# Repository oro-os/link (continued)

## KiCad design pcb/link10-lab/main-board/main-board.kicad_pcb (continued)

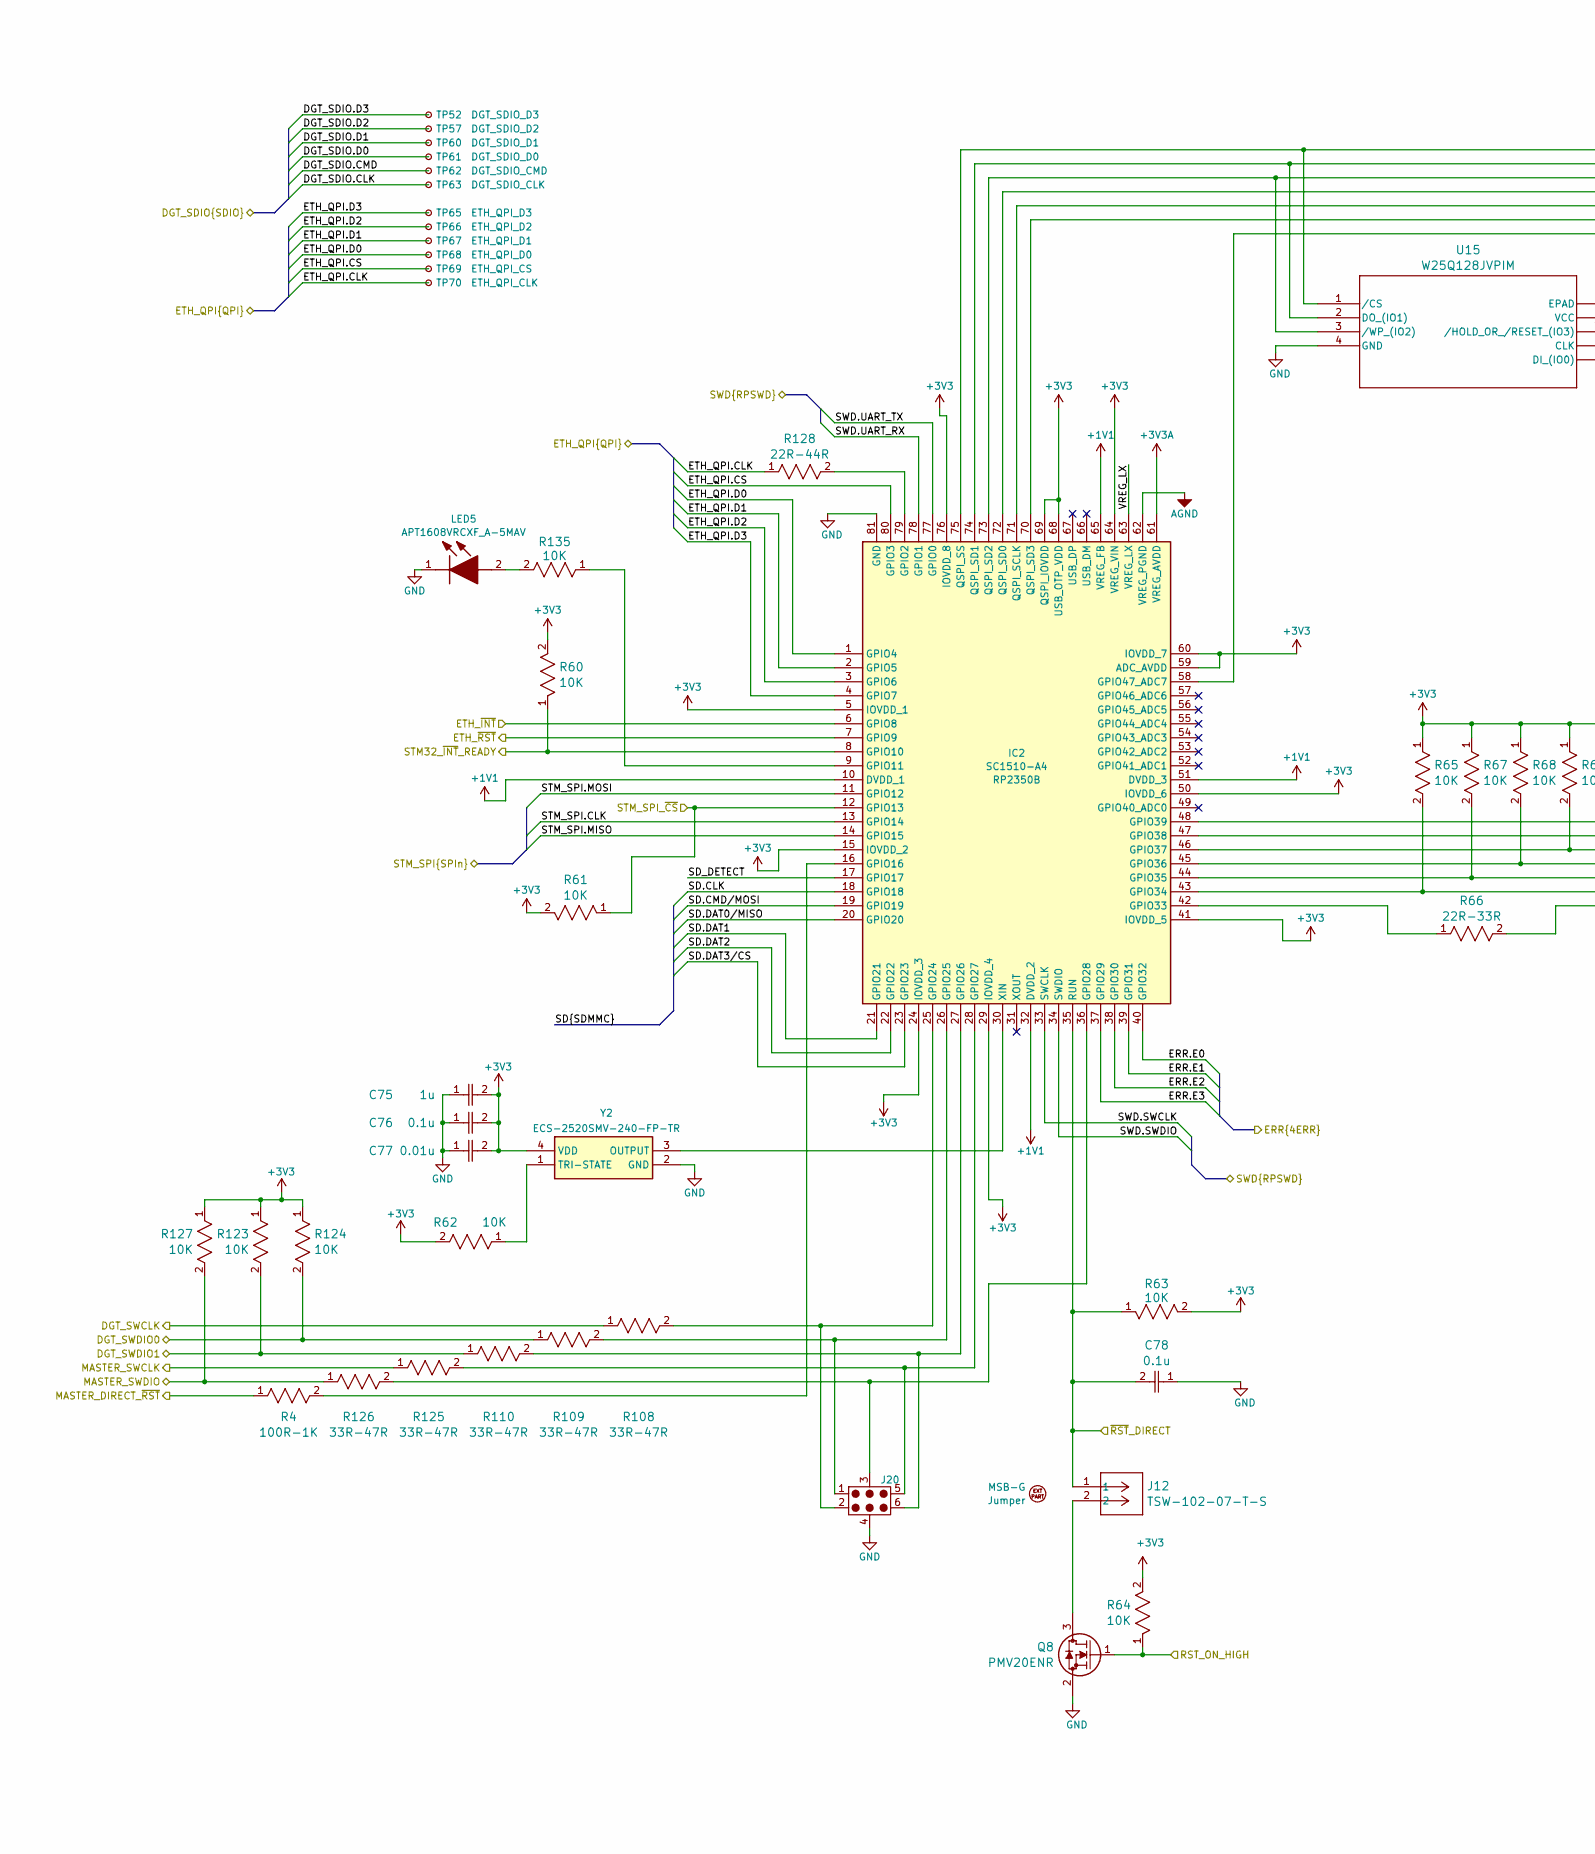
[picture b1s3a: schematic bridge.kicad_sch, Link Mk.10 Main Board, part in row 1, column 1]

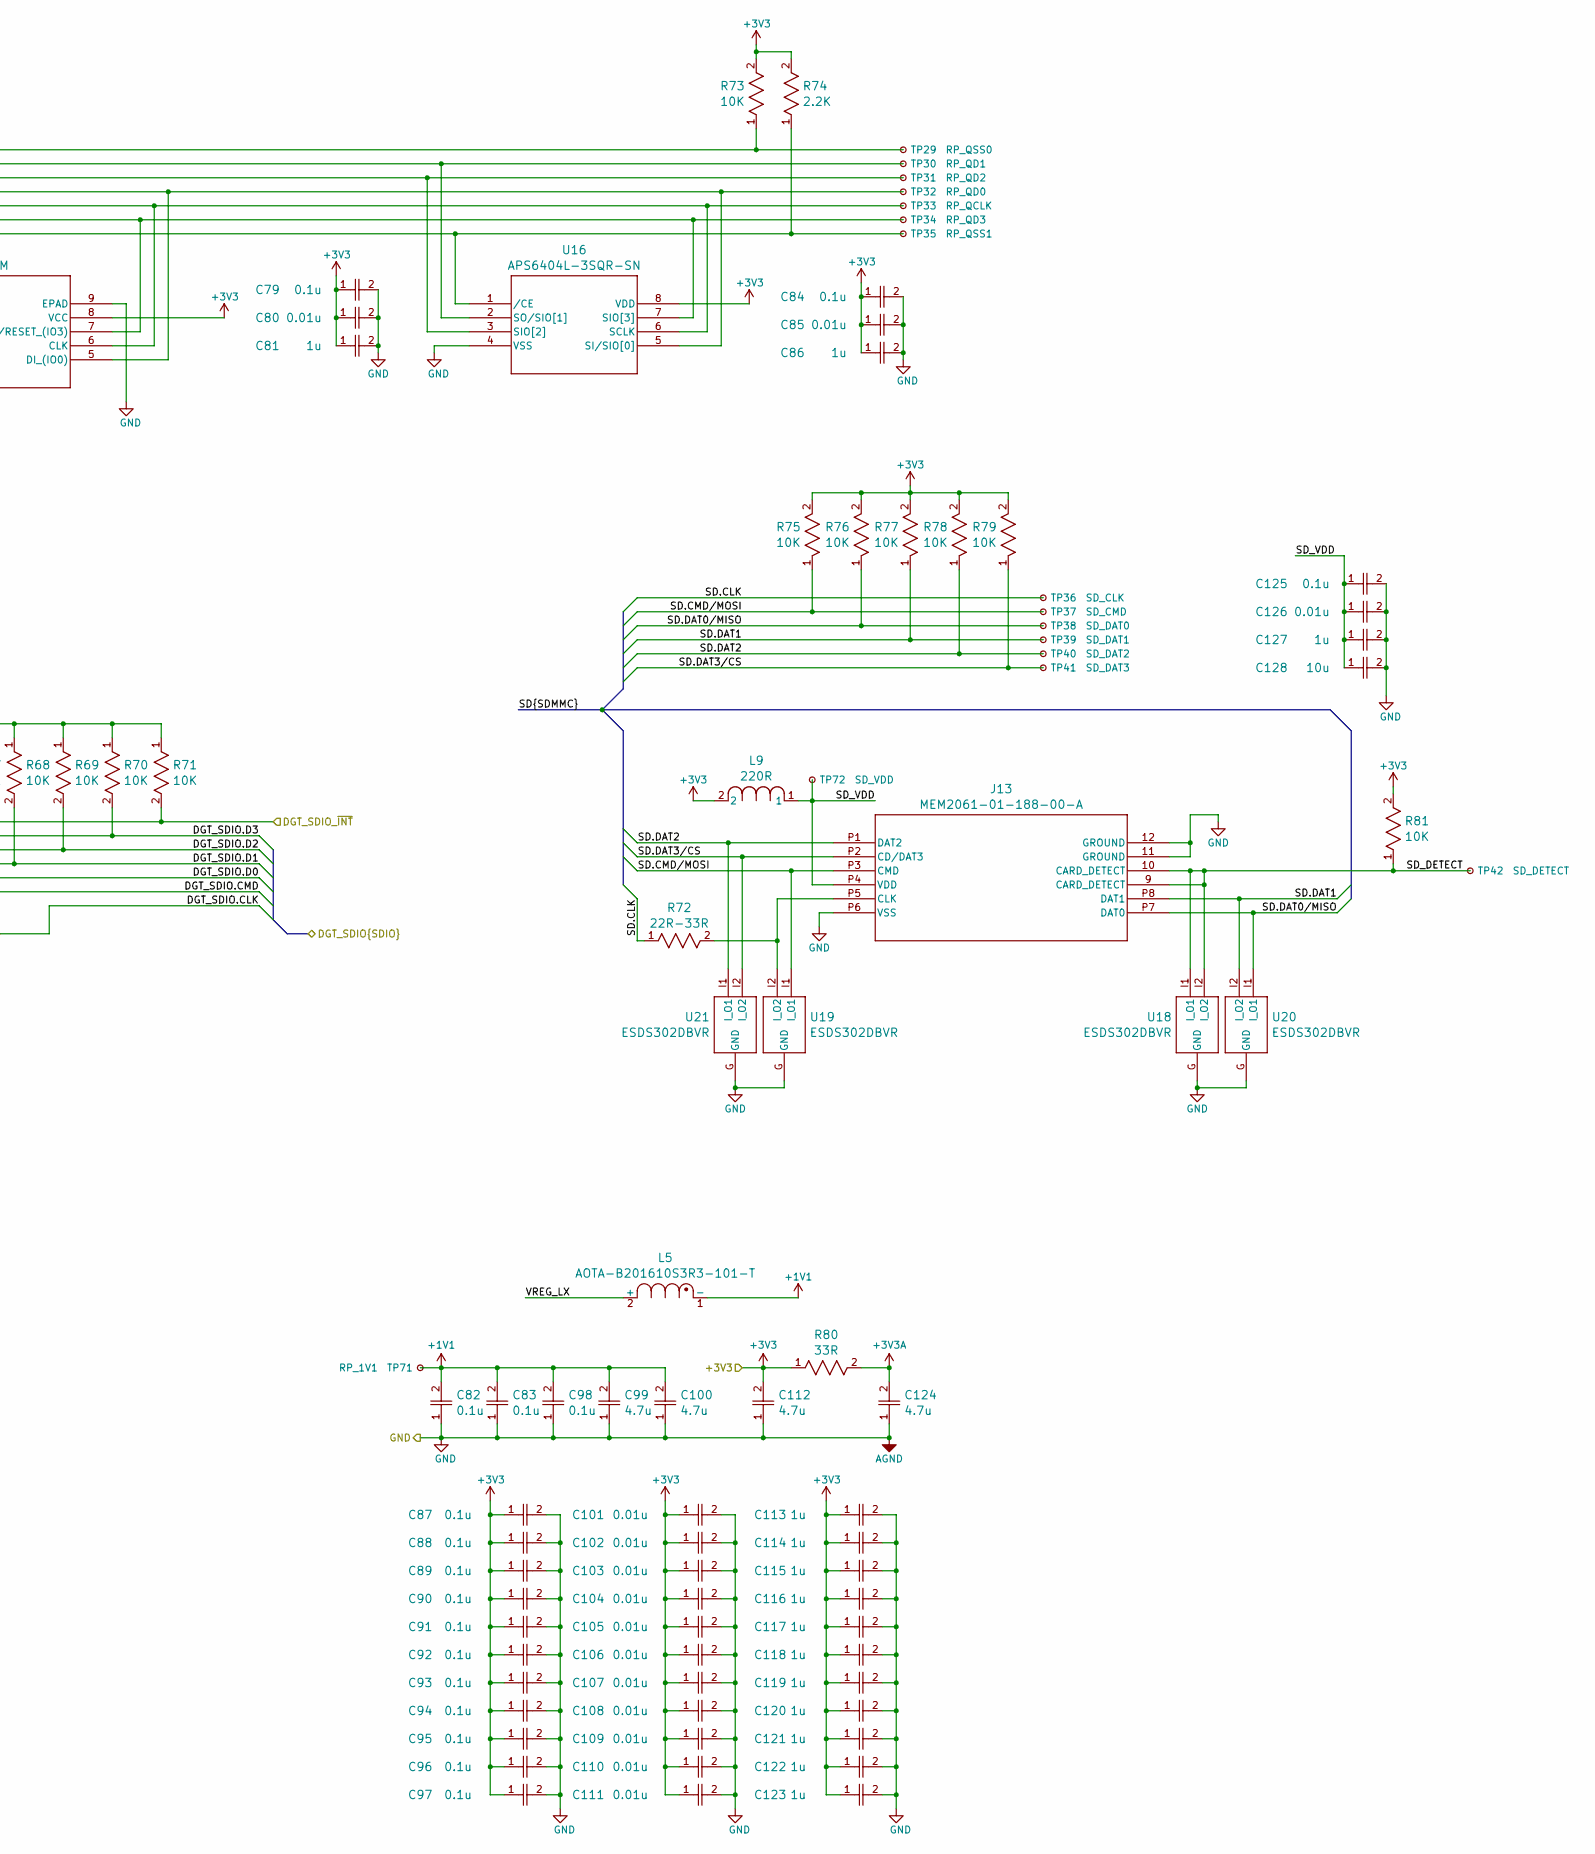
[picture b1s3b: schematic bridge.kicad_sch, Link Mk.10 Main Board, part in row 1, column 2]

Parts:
C75, C81, C86, C113, C114, C115, C116, C117, C118, C119, C120, C121, C122, C123, C127: 1u; OP_0001R; DigiKey ID 587-3766-1-ND
C76, C78, C79, C82, C83, C84, C87, C88, C89, C90, C91, C92, C93, C94, C95, C96, C97, C98, C125: 0.1u; OP_0001Y; DigiKey ID 587-MSAST1L3YB5104KFNA01CT-ND
C77, C80, C85, C101, C102, C103, C104, C105, C106, C107, C108, C109, C110, C111, C126: 0.01u; OP_0000F; Mouser ID 791-0402B103J160CT
C99, C100, C112, C124: 4.7u; OP_00014; Manufacturer_Part_Number GRM155C61E475ME15J; DigiKey ID 1276-1480-6-ND
C128: 10u; OP_0001M; Mouser P/N 81-GRM188R61E106MA3D; Mouser ID 81-GRM188R61E106MA3D
EXT4: MSB-G; Mouser P/N 737-MSB-G; Digi-Key P/N 2057-MSB-G-ND
IC2: SC1510-A4; OP_00050; Manufacturer_Part_Number SC1510-A4; Digi-Key P/N 2648-SC1510-A4CT-ND, 2648-SC1510-A4DKR-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
J12: TSW-102-07-T-S; OP_00079; Mouser P/N 200-TSW10207TS; Digi-Key P/N 612-TSW-102-07-T-S-ND
J13: MEM2061-01-188-00-A; OP_0001X; Mouser ID 640-MEM20610118800A
J20: CPG-81-TH-B-Pads; CPG-81-TH-B-Landing
L5: AOTA-B201610S3R3-101-T; OP_00073; Mouser P/N 815-AB201610S3R3101T; Digi-Key P/N 535-AOTA-B201610S3R3-101-TCT-ND, 535-AO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
L9: 220R; OP_0000Y; Mouser P/N 81-BLM18PG221SN1D; DigiKey ID 490-5221-1-ND
LED5: APT1608VRCXF_A-5MAV; OP_0000U; Manufacturer_Part_Number APT1608VRCXF/A-5MAV; Mouser Part Number 604-APT1608VRCXF5MAV
Q8: PMV20ENR; OP_0001Z; DigiKey ID 1727-2301-1-ND
R4: 100R-1K; OP_0003D; Mouser P/N 660-SG73P2ATTD102J; Digi-Key P/N 2019-SG73P2ATTD102JCT-ND, 2019-SG73P2AT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
R60, R61, R62, R63, R64, R65, R67, R68, R69, R70, R71, R73, R75, R76, R77, R78, R79, R81, R123, R124, R127, R135: 10K; OP_00021; DigiKey ID RMCF0402FT10K0CT-ND
R66, R72: 22R-33R; OP_00022; Mouser P/N 754-RR0510R-330D; DigiKey ID RR05R33DCT-ND
R74: 2.2K; OP_0002S; Mouser P/N 667-ERJ-P06F2321V; Digi-Key P/N ERJ-P06F2321V-ND
R80: 33R; OP_00022; Mouser P/N 754-RR0510R-330D; DigiKey ID RR05R33DCT-ND
R108, R109, R110, R125, R126: 33R-47R; OP_0005Y; Mouser P/N 652-CR0603FX-43R2ELF; Digi-Key P/N CR0603-FX-43R2ELFCT-ND, CR0603-FX-43R2E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
R128: 22R-44R; OP_0005Y; Mouser P/N 652-CR0603FX-43R2ELF; Digi-Key P/N CR0603-FX-43R2ELFCT-ND, CR0603-FX-43R2E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
TP29: RP_QSS0; TestPoint_Pad_D1.0mm
TP30: RP_QD1; TestPoint_Pad_D1.0mm
TP31: RP_QD2; TestPoint_Pad_D1.0mm
TP32: RP_QD0; TestPoint_Pad_D1.0mm
TP33: RP_QCLK; TestPoint_Pad_D1.0mm
TP34: RP_QD3; TestPoint_Pad_D1.0mm
TP35: RP_QSS1; TestPoint_Pad_D1.0mm
TP36: SD_CLK; TestPoint_Pad_D1.0mm
TP37: SD_CMD; TestPoint_Pad_D1.0mm
TP38: SD_DAT0; TestPoint_Pad_D1.0mm
TP39: SD_DAT1; TestPoint_Pad_D1.0mm
TP40: SD_DAT2; TestPoint_Pad_D1.0mm
TP41: SD_DAT3; TestPoint_Pad_D1.0mm
TP42: SD_DETECT; TestPoint_Pad_D1.0mm
TP52: DGT_SDIO_D3; TestPoint_Pad_D1.0mm
TP57: DGT_SDIO_D2; TestPoint_Pad_D1.0mm
TP60: DGT_SDIO_D1; TestPoint_Pad_D1.0mm
TP61: DGT_SDIO_D0; TestPoint_Pad_D1.0mm
TP62: DGT_SDIO_CMD; TestPoint_Pad_D1.0mm
TP63: DGT_SDIO_CLK; TestPoint_Pad_D1.0mm
TP65: ETH_QPI_D3; TestPoint_Pad_D1.0mm
TP66: ETH_QPI_D2; TestPoint_Pad_D1.0mm
TP67: ETH_QPI_D1; TestPoint_Pad_D1.0mm
TP68: ETH_QPI_D0; TestPoint_Pad_D1.0mm
TP69: ETH_QPI_CS; TestPoint_Pad_D1.0mm
TP70: ETH_QPI_CLK; TestPoint_Pad_D1.0mm
TP71: RP_1V1; TestPoint_Pad_2.0x2.0mm
TP72: SD_VDD; TestPoint_Pad_2.0x2.0mm
U15: W25Q128JVPIM; OP_00054; Mouser P/N 454-W25Q128JVPIMTR; Digi-Key P/N 256-W25Q128JVPIM-TUBE-ND, 256-W25Q128JV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
U16: APS6404L-3SQR-SN; OP_00055; Mouser P/N 878-APS6404L-3SQR-SN
U18, U19, U20, U21: ESDS302DBVR; OP_0003B; Mouser P/N 595-ESDS302DBVR; Digi-Key P/N 296-51110-1-ND, 296-51110-2-ND, 296-511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
Y2: ECS-2520SMV-240-FP-TR; OP_0001E; Manufacturer_Part_Number ECS-2520SMV-240-FP-TR; Mouser Part Number 520-2520SMV-240-FP-T

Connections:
+3V3_STM: C75.2, C76.2, C77.2, C79.1, C80.1, C81.1, C84.1, C85.1, C86.1, C87.1, C88.1, C89.1, C90.1, C91.1, C92.1, C93.1, C94.1, C95.1, C96.1, C97.1, C101.1, C102.1, C103.1, C104.1, C105.1, C106.1, C107.1, C108.1, C109.1, C110.1, C111.1, C112.2, C113.1, C114.1, C115.1, C116.1, C117.1, C118.1, C119.1, C120.1, C121.1, C122.1, C123.1, IC2.5 (IOVDD_1), IC2.15 (IOVDD_2), IC2.24 (IOVDD_3), IC2.29 (IOVDD_4), IC2.41 (IOVDD_5), IC2.50 (IOVDD_6), IC2.59 (ADC_AVDD), IC2.60 (IOVDD_7), IC2.64 (VREG_VIN), IC2.68 (USB_OTP_VDD), IC2.69 (QSPI_IOVDD), IC2.76 (IOVDD_8), L9.2, R60.2, R61.2, R62.2, R63.2, R64.2, R65.1, R67.1, R68.1, R69.1, R70.1, R71.1, R73.2, R74.2, R75.2, R76.2, R77.2, R78.2, R79.2, R80.1, R81.2, R123.1, R124.1, R127.1, U15.8 (VCC), U16.8 (VDD), Y2.4 (VDD); also elsewhere on the board
/BRIDGE_DIRECT_RST: C78.2, IC2.35 (RUN), J12.1, R63.1; also elsewhere on the board
/BRIDGE_INT: IC2.8 (GPIO10), R60.1; also elsewhere on the board
/BRIDGE_SWD.SWCLK: IC2.33 (SWCLK); also elsewhere on the board
/BRIDGE_SWD.SWDIO: IC2.34 (SWDIO); also elsewhere on the board
/BRIDGE_SWD.UART_RX: IC2.78 (GPIO1); also elsewhere on the board
/BRIDGE_SWD.UART_TX: IC2.77 (GPIO0); also elsewhere on the board
/Baseboard/RP_ERR.E0: IC2.40 (GPIO32); also elsewhere on the board
/Baseboard/RP_ERR.E1: IC2.39 (GPIO31); also elsewhere on the board
/Baseboard/RP_ERR.E2: IC2.38 (GPIO30); also elsewhere on the board
/Baseboard/RP_ERR.E3: IC2.37 (GPIO29); also elsewhere on the board
/Baseboard/SPI1.CLK: IC2.13 (GPIO14); also elsewhere on the board
/Baseboard/SPI1.MISO: IC2.14 (GPIO15); also elsewhere on the board
/Baseboard/SPI1.MOSI: IC2.11 (GPIO12); also elsewhere on the board
/Bridge (RP) + SD/+1V1: C82.2, C83.2, C98.2, C99.2, C100.2, IC2.10 (DVDD_1), IC2.32 (DVDD_2), IC2.51 (DVDD_3), IC2.65 (VREG_FB), L5.1 (-), TP71.1 (1_1)
/Bridge (RP) + SD/+3V3A: C124.2, IC2.61 (VREG_AVDD), R80.2
/Bridge (RP) + SD/DGT_SDIO.CLK: R66.2, TP63.1 (1_1); also elsewhere on the board
/Bridge (RP) + SD/DGT_SDIO.CMD: IC2.43 (GPIO34), R65.2, TP62.1 (1_1); also elsewhere on the board
/Bridge (RP) + SD/DGT_SDIO.D0: IC2.44 (GPIO35), R67.2, TP61.1 (1_1); also elsewhere on the board
/Bridge (RP) + SD/DGT_SDIO.D1: IC2.45 (GPIO36), R68.2, TP60.1 (1_1); also elsewhere on the board
/Bridge (RP) + SD/DGT_SDIO.D2: IC2.46 (GPIO37), R69.2, TP57.1 (1_1); also elsewhere on the board
/Bridge (RP) + SD/DGT_SDIO.D3: IC2.47 (GPIO38), R70.2, TP52.1 (1_1); also elsewhere on the board
/Bridge (RP) + SD/DGT_SWCLK: R108.1; also elsewhere on the board
/Bridge (RP) + SD/DGT_SWDIO0: R109.1, R124.2; also elsewhere on the board
/Bridge (RP) + SD/DGT_SWDIO1: R110.1, R123.2; also elsewhere on the board
/Bridge (RP) + SD/ETH_QPI.CLK: R128.1, TP70.1 (1_1); also elsewhere on the board
/Bridge (RP) + SD/ETH_QPI.CS: IC2.80 (GPIO3), TP69.1 (1_1); also elsewhere on the board
/Bridge (RP) + SD/ETH_QPI.D0: IC2.1 (GPIO4), TP68.1 (1_1); also elsewhere on the board
/Bridge (RP) + SD/ETH_QPI.D1: IC2.2 (GPIO5), TP67.1 (1_1); also elsewhere on the board
/Bridge (RP) + SD/ETH_QPI.D2: IC2.3 (GPIO6), TP66.1 (1_1); also elsewhere on the board
/Bridge (RP) + SD/ETH_QPI.D3: IC2.4 (GPIO7), TP65.1 (1_1); also elsewhere on the board
/Bridge (RP) + SD/ETH_~INT: IC2.6 (GPIO8); also elsewhere on the board
/Bridge (RP) + SD/ETH_~RST: IC2.7 (GPIO9); also elsewhere on the board
/Bridge (RP) + SD/SD.CLK: IC2.18 (GPIO18), R72.1, TP36.1 (1_1)
/Bridge (RP) + SD/SD.CMD/MOSI: IC2.19 (GPIO19), J13.P3 (CMD), R75.1, TP37.1 (1_1), U19.I1 (I_O1)
/Bridge (RP) + SD/SD.DAT0/MISO: IC2.20 (GPIO20), J13.P7 (DAT0), R76.1, TP38.1 (1_1), U20.I1 (I_O1)
/Bridge (RP) + SD/SD.DAT1: IC2.21 (GPIO21), J13.P8 (DAT1), R77.1, TP39.1 (1_1), U20.I2 (I_O2)
/Bridge (RP) + SD/SD.DAT2: IC2.22 (GPIO22), J13.P1 (DAT2), R78.1, TP40.1 (1_1), U21.I1 (I_O1)
/Bridge (RP) + SD/SD.DAT3/CS: IC2.23 (GPIO23), J13.P2 (CD/DAT3), R79.1, TP41.1 (1_1), U21.I2 (I_O2)
/Bridge (RP) + SD/SD_DETECT: IC2.17 (GPIO17), J13.9 (CARD_DETECT), J13.10 (CARD_DETECT), R81.1, TP42.1 (1_1), U18.I1 (I_O1), U18.I2 (I_O2)
/Bridge (RP) + SD/SD_VDD: C125.1, C126.1, C127.1, C128.1, J13.P4 (VDD), L9.1, TP72.1 (1_1)
/Bridge (RP) + SD/STM_SPI_~CS: IC2.12 (GPIO13), R61.1; also elsewhere on the board
/Bridge (RP) + SD/VREG_LX: IC2.63 (VREG_LX), L5.2 (+)
/DGT_SDIO_INT: IC2.48 (GPIO39), R71.2; also elsewhere on the board
/MASTER_DIRECT_RST: R4.1; also elsewhere on the board
/MASTER_SWD.SWCLK: R125.1; also elsewhere on the board
/MASTER_SWD.SWDIO: R126.1, R127.2; also elsewhere on the board
/RP_BB_RST: Q8.1 (G), R64.1; also elsewhere on the board
GND: C75.1, C76.1, C77.1, C78.1, C79.2, C80.2, C81.2, C82.1, C83.1, C84.2, C85.2, C86.2, C87.2, C88.2, C89.2, C90.2, C91.2, C92.2, C93.2, C94.2, C95.2, C96.2, C97.2, C98.1, C99.1, C100.1, C101.2, C102.2, C103.2, C104.2, C105.2, C106.2, C107.2, C108.2, C109.2, C110.2, C111.2, C112.1, C113.2, C114.2, C115.2, C116.2, C117.2, C118.2, C119.2, C120.2, C121.2, C122.2, C123.2, C124.1, C125.2, C126.2, C127.2, C128.2, IC2.62 (VREG_PGND), IC2.81 (GND), J13.11 (GROUND), J13.12 (GROUND), J13.P6 (VSS), J20.4, LED5.1 (K), Q8.2 (S), U15.4 (GND), U15.9 (EPAD), U16.4 (VSS), U18.G (GND), U19.G (GND), U20.G (GND), U21.G (GND), Y2.2 (GND); also elsewhere on the board
unnamed: IC2.79 (GPIO2), R128.2
unnamed: IC2.9 (GPIO11), R135.1
unnamed: IC2.16 (GPIO16), R4.2
unnamed: IC2.25 (GPIO24), J20.2, R108.2
unnamed: IC2.26 (GPIO25), J20.1, R109.2
unnamed: IC2.27 (GPIO26), J20.6, R110.2
unnamed: IC2.28 (GPIO27), J20.5, R125.2
unnamed: IC2.36 (GPIO28), J20.3, R126.2
unnamed: IC2.42 (GPIO33), R66.1
unnamed: IC2.58 (GPIO47_ADC7), R74.1, TP35.1 (1_1), U16.1 (/CE)
unnamed: IC2.71 (QSPI_SCLK), TP33.1 (1_1), U15.6 (CLK), U16.6 (SCLK)
unnamed: IC2.72 (QSPI_SD0), TP32.1 (1_1), U15.5 (DI_(IO0)), U16.5 (SI/SIO[0])
unnamed: IC2.74 (QSPI_SD1), TP30.1 (1_1), U15.2 (DO_(IO1)), U16.2 (SO/SIO[1])
unnamed: IC2.73 (QSPI_SD2), TP31.1 (1_1), U15.3 (/WP_(IO2)), U16.3 (SIO[2])
unnamed: IC2.70 (QSPI_SD3), TP34.1 (1_1), U15.7 (/HOLD_OR_/RESET_(IO3)), U16.7 (SIO[3])
unnamed: IC2.75 (QSPI_SS), R73.1, TP29.1 (1_1), U15.1 (/CS)
unnamed: IC2.30 (XIN), Y2.3 (OUTPUT)
unnamed: J13.P5 (CLK), R72.2, U19.I2 (I_O2)
unnamed: LED5.2 (A), R135.2
unnamed: J12.2, Q8.3 (D)
unnamed: R62.1, Y2.1 (TRI-STATE)

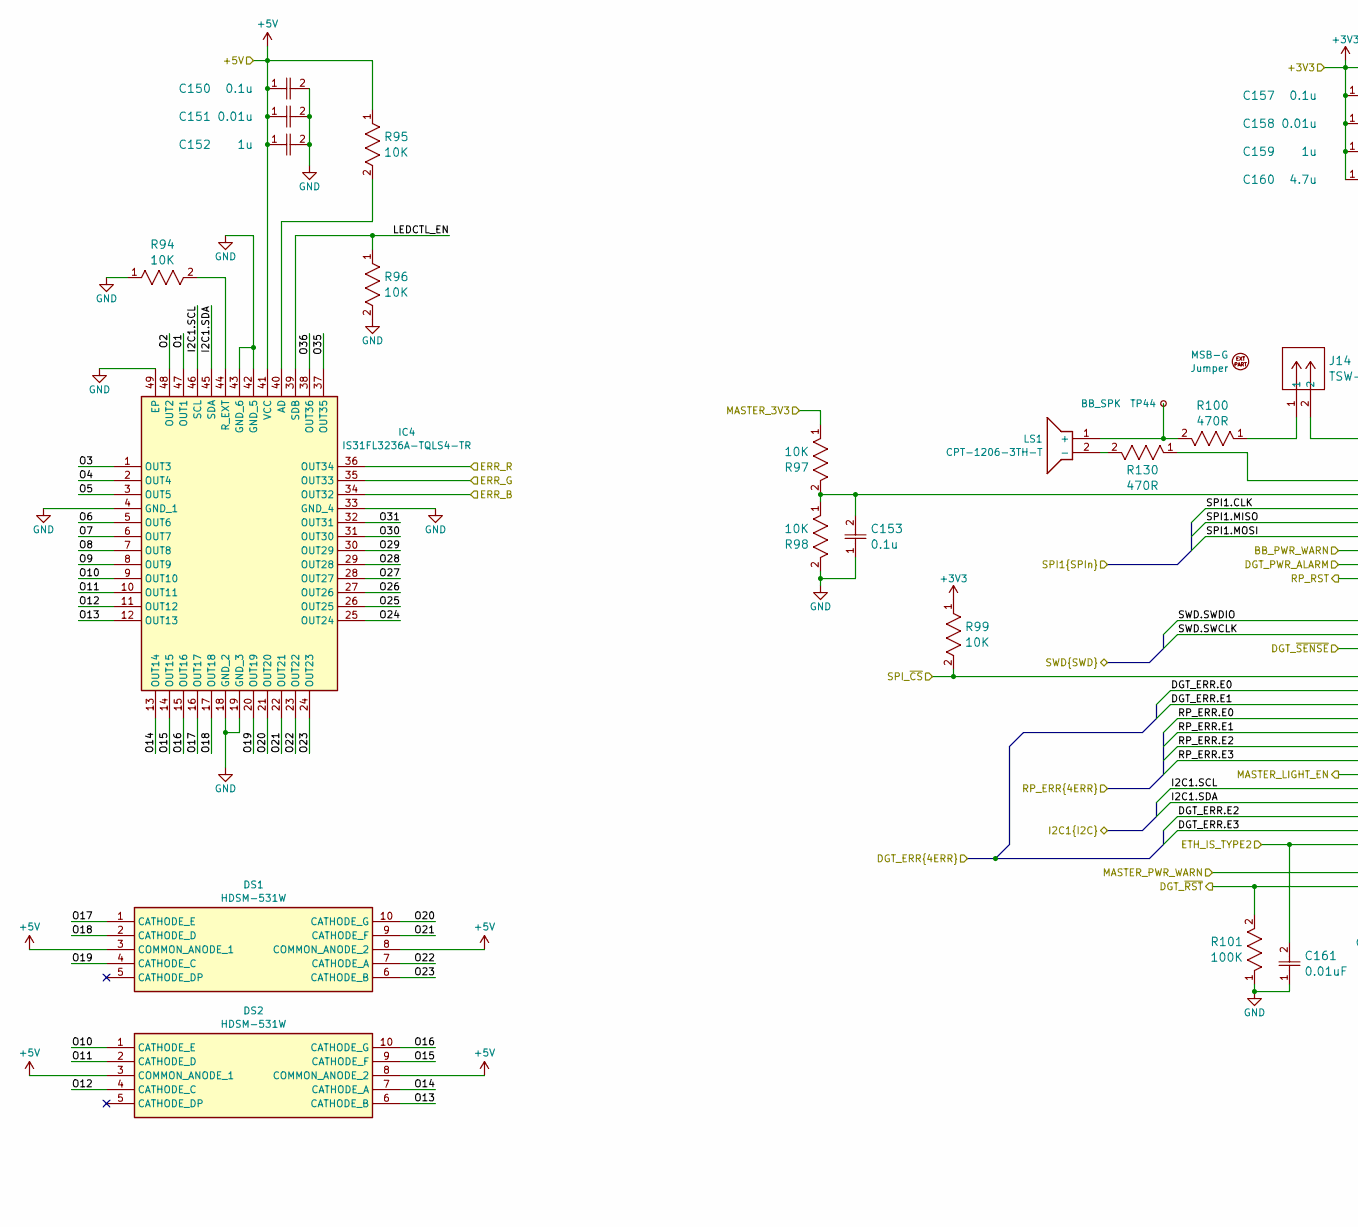
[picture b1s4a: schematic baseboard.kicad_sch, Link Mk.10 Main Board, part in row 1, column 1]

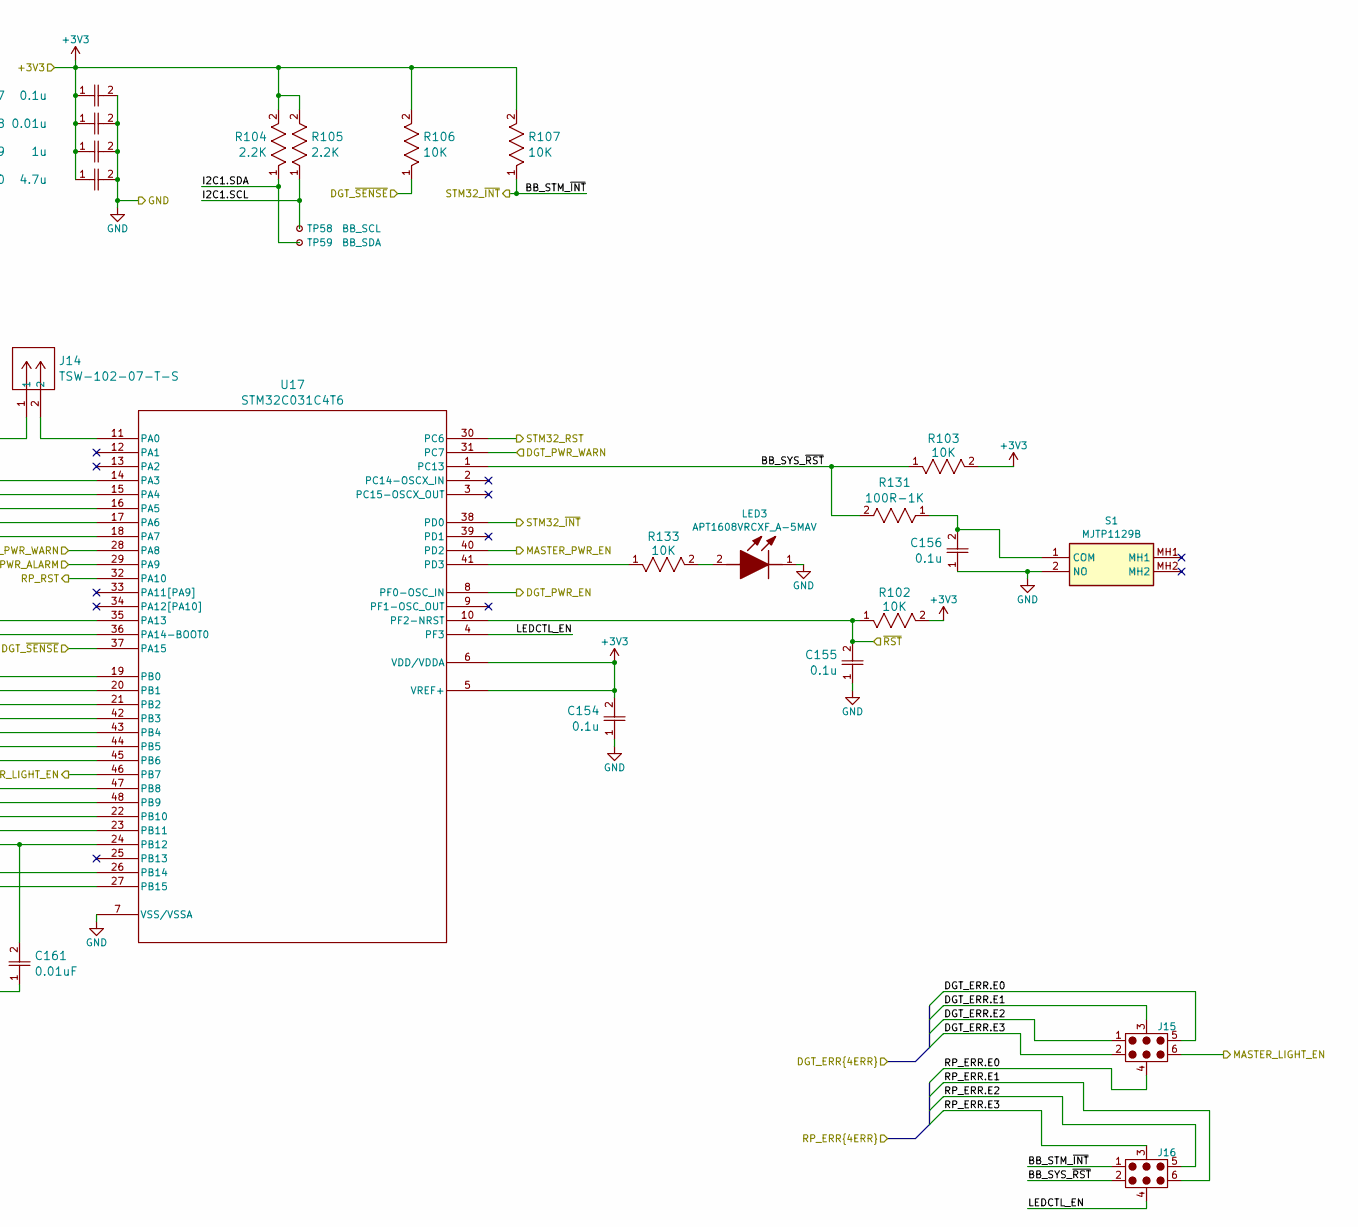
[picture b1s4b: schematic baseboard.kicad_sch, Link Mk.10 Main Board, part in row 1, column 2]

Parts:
C150, C153, C154, C155, C156, C157: 0.1u; OP_0001Y; DigiKey ID 587-MSAST1L3YB5104KFNA01CT-ND
C151, C158: 0.01u; OP_0000F; Mouser ID 791-0402B103J160CT
C152, C159: 1u; OP_0001R; DigiKey ID 587-3766-1-ND
C160: 4.7u; OP_00014; Manufacturer_Part_Number GRM155C61E475ME15J; DigiKey ID 1276-1480-6-ND
C161: 0.01uF; OP_0000F; Mouser ID 791-0402B103J160CT
DS1, DS2: HDSM-531W; OP_00077; Manufacturer_Part_Number HDSM-531W; Mouser Part Number 630-HDSM-531W
EXT5: MSB-G; Mouser P/N 737-MSB-G; Digi-Key P/N 2057-MSB-G-ND
IC4: IS31FL3236A-TQLS4-TR; OP_0001Q; Manufacturer_Part_Number IS31FL3236A-TQLS4-TR; Mouser Part Number 870-I31FL3236ATQLS4T
J14: TSW-102-07-T-S; OP_00079; Mouser P/N 200-TSW10207TS; Digi-Key P/N 612-TSW-102-07-T-S-ND
J15, J16: CPG-81-TH-B-Pads; CPG-81-TH-B-Landing
LED3: APT1608VRCXF_A-5MAV; OP_0000U; Manufacturer_Part_Number APT1608VRCXF/A-5MAV; Mouser Part Number 604-APT1608VRCXF5MAV
LS1: CPT-1206-3TH-T; OP_00078; Manufacturer_Part_Number CPT-1206-3TH-T; Digi-Key P/N 2223-CPT-1206-3TH-T-ND
R94, R95, R96, R97, R98, R99, R102, R103, R106, R107, R133: 10K; OP_00021; DigiKey ID RMCF0402FT10K0CT-ND
R100, R130: 470R; OP_00031; Mouser P/N 603-AC0805FR-07470RL; Digi-Key P/N YAG3733CT-ND, YAG3733DKR-ND, YAG3733TR-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
R101: 100K; OP_00066
R104, R105: 2.2K; OP_0002S; Mouser P/N 667-ERJ-P06F2321V; Digi-Key P/N ERJ-P06F2321V-ND
R131: 100R-1K; OP_0003D; Mouser P/N 660-SG73P2ATTD102J; Digi-Key P/N 2019-SG73P2ATTD102JCT-ND, 2019-SG73P2AT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
S1: MJTP1129B; OP_0005B; Manufacturer_Part_Number MJTP1129B; Mouser Part Number 642-MJTP1129B
TP44: BB_SPK; TestPoint_Pad_2.0x2.0mm
TP58: BB_SCL; TestPoint_Pad_D1.0mm
TP59: BB_SDA; TestPoint_Pad_D1.0mm
U17: STM32C031C4T6; OP_00076; Mouser P/N 511-STM32C031C4T6; Digi-Key P/N 497-STM32C031C4T6-ND

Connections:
+3V3_BASE: C154.2, C157.1, C158.1, C159.1, C160.1, R99.1, R102.2, R103.2, R104.2, R105.2, R106.2, R107.2, U17.5 (VREF+), U17.6 (VDD/VDDA); also elsewhere on the board
+3V3_STM: R97.1; also elsewhere on the board
+5V_BASE: C150.1, C151.1, C152.1, DS1.3 (COMMON_ANODE_1), DS1.8 (COMMON_ANODE_2), DS2.3 (COMMON_ANODE_1), DS2.8 (COMMON_ANODE_2), IC4.41 (VCC), R95.1; also elsewhere on the board
/BB_I2C1.SCL: IC4.46 (SCL), R105.1, TP58.1 (1_1), U17.47 (PB8); also elsewhere on the board
/BB_I2C1.SDA: IC4.45 (SDA), R104.1, TP59.1 (1_1), U17.48 (PB9); also elsewhere on the board
/BB_RST: C155.2, R102.1, U17.10 (PF2-NRST); also elsewhere on the board
/BB_SWD.SWCLK: U17.36 (PA14-BOOT0); also elsewhere on the board
/BB_SWD.SWDIO: U17.35 (PA13); also elsewhere on the board
/Baseboard/BB_PWR_WARN: U17.28 (PA8); also elsewhere on the board
/Baseboard/BB_STM_~INT: J16.1, R107.1, U17.38 (PD0); also elsewhere on the board
/Baseboard/BB_SYS_~RST: J16.2, R103.1, R131.2, U17.1 (PC13)
/Baseboard/DGT_ERR.E0: J15.5, U17.20 (PB1); also elsewhere on the board
/Baseboard/DGT_ERR.E1: J15.3, U17.21 (PB2); also elsewhere on the board
/Baseboard/DGT_ERR.E2: J15.1, U17.22 (PB10); also elsewhere on the board
/Baseboard/DGT_ERR.E3: J15.2, U17.23 (PB11); also elsewhere on the board
/Baseboard/DGT_PWR_ALARM: U17.29 (PA9); also elsewhere on the board
/Baseboard/DGT_PWR_EN: U17.8 (PF0-OSC_IN); also elsewhere on the board
/Baseboard/DGT_PWR_WARN: U17.31 (PC7); also elsewhere on the board
/Baseboard/ERR_B: IC4.34 (OUT32); also elsewhere on the board
/Baseboard/ERR_G: IC4.35 (OUT33); also elsewhere on the board
/Baseboard/ERR_R: IC4.36 (OUT34); also elsewhere on the board
/Baseboard/ETH_IS_TYPE2: C161.2, U17.24 (PB12); also elsewhere on the board
/Baseboard/LEDCTL_EN: IC4.39 (SDB), J16.4, R96.1, U17.4 (PF3)
/Baseboard/MASTER_LIGHT_EN: J15.6, U17.46 (PB7); also elsewhere on the board
/Baseboard/MASTER_PWR_EN: U17.40 (PD2); also elsewhere on the board
/Baseboard/MASTER_PWR_WARN: U17.26 (PB14); also elsewhere on the board
/Baseboard/O1: IC4.47 (OUT1)
/Baseboard/O2: IC4.48 (OUT2)
/Baseboard/O3: IC4.1 (OUT3)
/Baseboard/O4: IC4.2 (OUT4)
/Baseboard/O5: IC4.3 (OUT5)
/Baseboard/O6: IC4.5 (OUT6)
/Baseboard/O7: IC4.6 (OUT7)
/Baseboard/O8: IC4.7 (OUT8)
/Baseboard/O9: IC4.8 (OUT9)
/Baseboard/O10: DS2.1 (CATHODE_E), IC4.9 (OUT10)
/Baseboard/O11: DS2.2 (CATHODE_D), IC4.10 (OUT11)
/Baseboard/O12: DS2.4 (CATHODE_C), IC4.11 (OUT12)
/Baseboard/O13: DS2.6 (CATHODE_B), IC4.12 (OUT13)
/Baseboard/O14: DS2.7 (CATHODE_A), IC4.13 (OUT14)
/Baseboard/O15: DS2.9 (CATHODE_F), IC4.14 (OUT15)
/Baseboard/O16: DS2.10 (CATHODE_G), IC4.15 (OUT16)
/Baseboard/O17: DS1.1 (CATHODE_E), IC4.16 (OUT17)
/Baseboard/O18: DS1.2 (CATHODE_D), IC4.17 (OUT18)
/Baseboard/O19: DS1.4 (CATHODE_C), IC4.20 (OUT19)
/Baseboard/O20: DS1.10 (CATHODE_G), IC4.21 (OUT20)
/Baseboard/O21: DS1.9 (CATHODE_F), IC4.22 (OUT21)
/Baseboard/O22: DS1.7 (CATHODE_A), IC4.23 (OUT22)
/Baseboard/O23: DS1.6 (CATHODE_B), IC4.24 (OUT23)
/Baseboard/O24: IC4.25 (OUT24)
/Baseboard/O25: IC4.26 (OUT25)
/Baseboard/O26: IC4.27 (OUT26)
/Baseboard/O27: IC4.28 (OUT27)
/Baseboard/O28: IC4.29 (OUT28)
/Baseboard/O29: IC4.30 (OUT29)
/Baseboard/O30: IC4.31 (OUT30)
/Baseboard/O31: IC4.32 (OUT31)
/Baseboard/O35: IC4.37 (OUT35)
/Baseboard/O36: IC4.38 (OUT36)
/Baseboard/RP_ERR.E0: J15.4, U17.42 (PB3); also elsewhere on the board
/Baseboard/RP_ERR.E1: J16.6, U17.43 (PB4); also elsewhere on the board
/Baseboard/RP_ERR.E2: J16.5, U17.44 (PB5); also elsewhere on the board
/Baseboard/RP_ERR.E3: J16.3, U17.45 (PB6); also elsewhere on the board
/Baseboard/SPI1.CLK: U17.16 (PA5); also elsewhere on the board
/Baseboard/SPI1.MISO: U17.17 (PA6); also elsewhere on the board
/Baseboard/SPI1.MOSI: U17.18 (PA7); also elsewhere on the board
/Baseboard/SPI_~CS: R99.2, U17.19 (PB0); also elsewhere on the board
/Baseboard/STM32_RST: U17.30 (PC6); also elsewhere on the board
/DGT_RST: R101.2, U17.27 (PB15); also elsewhere on the board
/DGT_SENSE: R106.1, U17.37 (PA15); also elsewhere on the board
/RP_BB_RST: U17.32 (PA10); also elsewhere on the board
GND: C150.2, C151.2, C152.2, C153.1, C154.1, C155.1, C156.1, C157.2, C158.2, C159.2, C160.2, C161.1, IC4.4 (GND_1), IC4.18 (GND_2), IC4.19 (GND_3), IC4.33 (GND_4), IC4.42 (GND_5), IC4.43 (GND_6), IC4.49 (EP), LED3.1 (K), R94.1, R96.2, R98.2, R101.1, S1.2 (NO), U17.7 (VSS/VSSA); also elsewhere on the board
unnamed: IC4.40 (AD), R95.2
unnamed: IC4.44 (R_EXT), R94.2
unnamed: J14.1, R100.1
unnamed: LED3.2 (A), R133.2
unnamed: LS1.1 (+), R100.2, TP44.1 (1_1)
unnamed: LS1.2 (-), R130.2
unnamed: C156.2, R131.1, S1.1 (COM)
unnamed: J14.2, U17.11 (PA0)
unnamed: R130.1, U17.14 (PA3)
unnamed: C153.2, R97.2, R98.1, U17.15 (PA4)
unnamed: R133.1, U17.41 (PD3)
